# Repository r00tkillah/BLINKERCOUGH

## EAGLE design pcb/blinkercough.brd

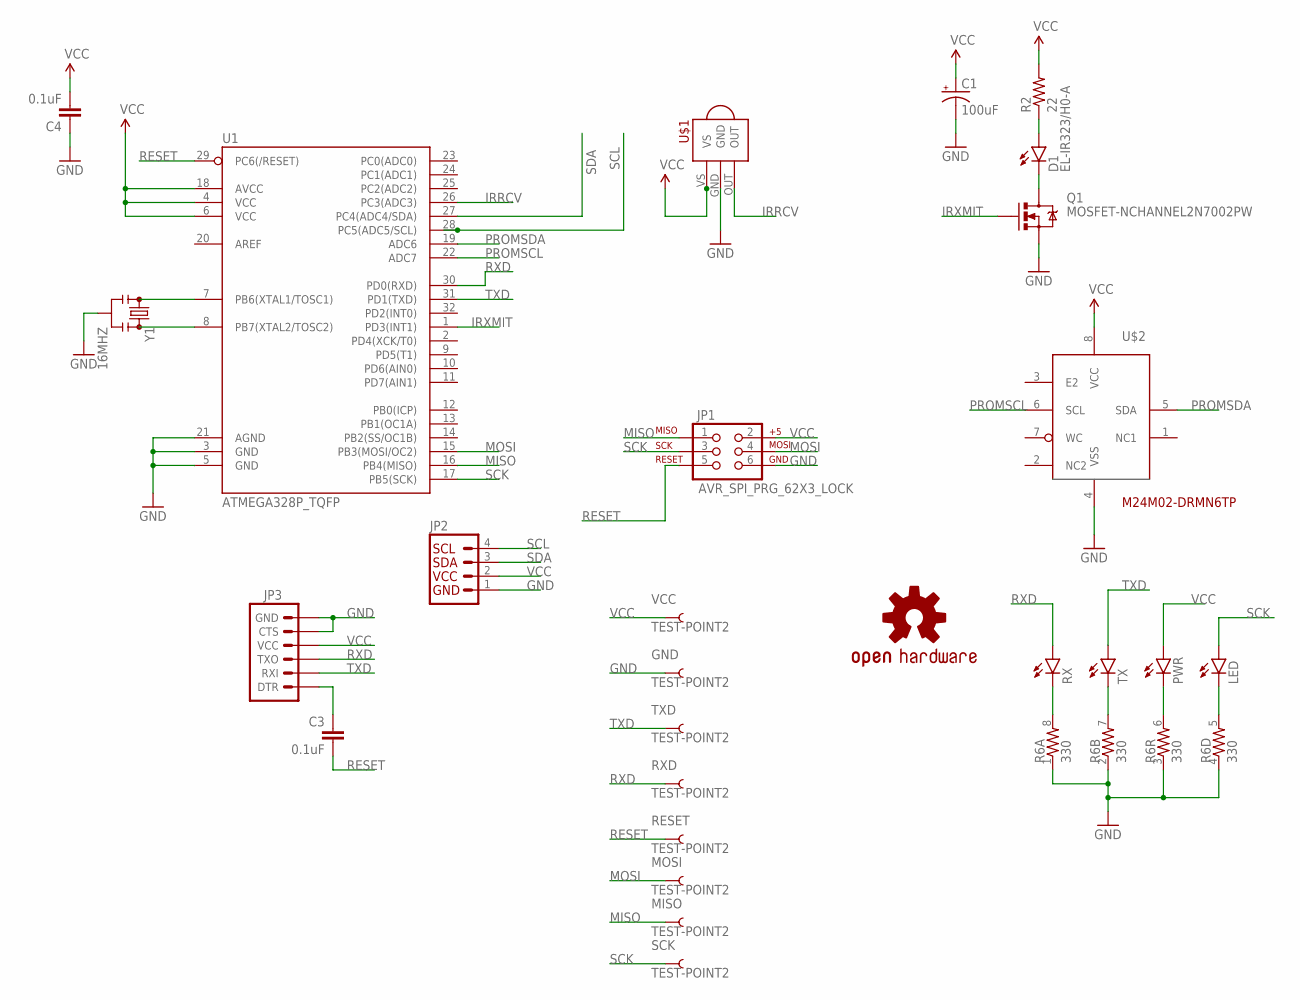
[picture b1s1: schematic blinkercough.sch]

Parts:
C1: 100uF; EIA7343
C3, C4: 0.1uF; 0603-CAP
D1: EL-IR323/H0-A; LED3MM
GND: TEST-POINT2; PAD.02X.02
JP1: AVR_SPI_PRG_62X3_LOCK; 2X3_LOCK
JP2: I2C_STANDARD; 1X04
JP3: ARDUINO_SERIAL_PROGRAMLOCK; 1X06_LOCK
LED: LED0603; LED-0603
LOGO1: OSHW-LOGOS; OSHW-LOGO-S
MISO: TEST-POINT2; PAD.02X.02
MOSI: TEST-POINT2; PAD.02X.02
PWR: LED0603; LED-0603
Q1: MOSFET-NCHANNEL2N7002PW; SOT323
R2: 22; 1206
R6: 330; 0603-ARV
RESET: TEST-POINT2; PAD.02X.02
RX: LED0603; LED-0603
RXD: TEST-POINT2; PAD.02X.02
SCK: TEST-POINT2; PAD.02X.02
TX: LED0603; LED-0603
TXD: TEST-POINT2; PAD.02X.02
U1: ATMEGA328P_TQFP; TQFP32-08
U$1: TSOP2438
U$2: M24M02-DRMN6TP; SO8
VCC: TEST-POINT2; PAD.02X.02
Y1: 16MHZ; RESONATOR-SMD

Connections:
GND: C1.C (-), C4.1, GND.P$1, JP1.6, JP2.1, JP3.5 (CTS), JP3.6 (GND), Q1.2 (S), R6.1, R6.2 (1), R6.3 (1), R6.4 (1), U1.3 (GND), U1.5 (GND), U1.21 (AGND), U$1.GND, U$2.4 (VSS), Y1.2
IRRCV: U1.26 (PC3(ADC3)), U$1.OUT
IRXMIT: Q1.1 (G), U1.1 (PD3(INT1))
LED: LED.C, R6.5 (2)
MISO: JP1.1, MISO.P$1, U1.16 (PB4(MISO))
MOSI: JP1.4, MOSI.P$1, U1.15 (PB3(MOSI/OC2))
unnamed: U1.7 (PB6(XTAL1/TOSC1)), Y1.1
unnamed: U1.8 (PB7(XTAL2/TOSC2)), Y1.3
unnamed: R6.8 (2), RX.C
unnamed: C3.1, JP3.1 (DTR)
unnamed: D1.K (C), Q1.3 (D)
unnamed: D1.A, R2.1
unnamed: R6.7 (2), TX.C
PROMSCL: U1.22 (ADC7), U$2.6 (SCL)
PROMSDA: U1.19 (ADC6), U$2.5 (SDA)
PWR: PWR.C, R6.6 (2)
RESET: C3.2, JP1.5, RESET.P$1, U1.29 (PC6(/RESET))
RXD: JP3.3 (TXO), RX.A, RXD.P$1, U1.30 (PD0(RXD))
SCK: JP1.3, LED.A, SCK.P$1, U1.17 (PB5(SCK))
SCL: JP2.4, U1.28 (PC5(ADC5/SCL))
SDA: JP2.3, U1.27 (PC4(ADC4/SDA))
TXD: JP3.2 (RXI), TX.A, TXD.P$1, U1.31 (PD1(TXD))
VCC: C1.A (+), C4.2, JP1.2, JP2.2, JP3.4 (VCC), PWR.A, R2.2, U1.4 (VCC), U1.6 (VCC), U1.18 (AVCC), U$1.VS, U$2.8 (VCC), VCC.P$1

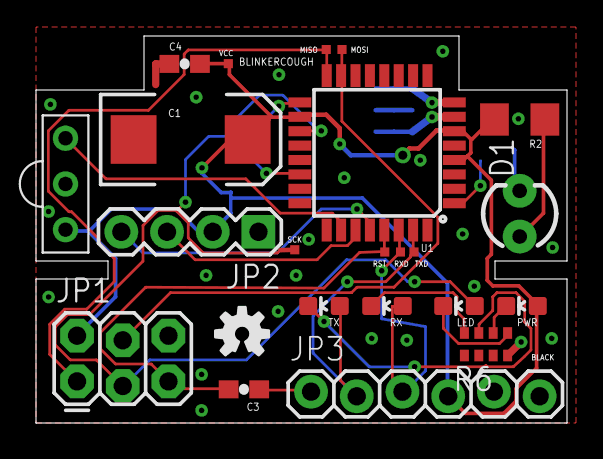
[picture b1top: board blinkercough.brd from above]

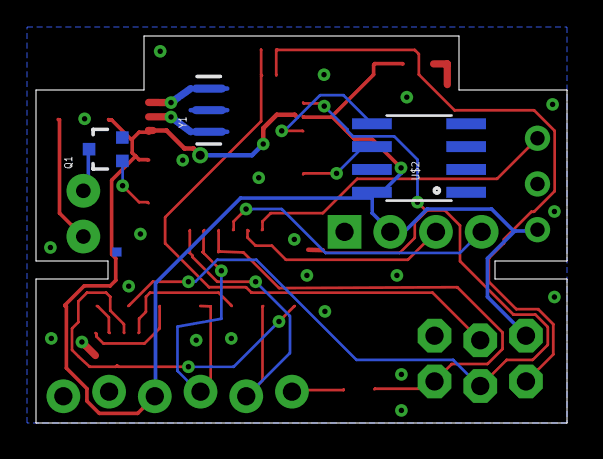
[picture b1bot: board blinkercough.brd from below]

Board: 2 copper layers, 29.5 x 21.5 mm, 27 parts (4 on the bottom side), 23 nets.

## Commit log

2015-08-10 Initial public push of BLINKERCOUGH
    BLINKERCOUGH is an NSA Playset project to bridge the airgap without
    radios. This was presented at BSidesLV 2015.
    There are still bugs with this release. This work is not finished.
2015-08-11 Adding eagle PCB design files
2015-08-21 fix submodules
    It appears that this was broken for new checkouts and I had failed to notice
2015-08-21 add address storage into eeprom to make life easier
2015-08-21 whitespace cleanup
2015-08-23 fix format string screwup in hexdump
2015-08-27 Fixes #3
    Actually it was not commander.py, but an off by one buffer length in
    the serial implementation of the registers in the main file.
2015-09-07 catch some cases where debug wasn't used right
2015-09-07 convert polling to repeat commands
    serial buffer is just 2 bytes. buffer was not serviced fast enough in
    some cases (cause not fully understood) and getting truncated. Now,
    if the command times out, we repeat.
2015-09-20 output when invalid command is recieved
2015-09-20 correct order of free in hooks
2015-09-20 Fix off by one errors
2015-09-20 switch to queing bytes via events
    takes queue operations out of the interrupt context in i2c
2015-09-20 add debug for buffer overrun
2015-09-20 zero out frame on alloc/free
2015-09-20 add reset() in some lost cases
2015-09-20 add debug where print was used
2015-09-20 less chatty
2015-09-20 make packet printing slightly easier to use
2015-09-20 correct sizing errors
    In various ways.. Ought to make this easier to read/use
2015-09-20 symbolic size calculation
    Easier to read?
2015-09-20 another math error
2015-09-20 add poll_for to poll for specific times
2015-09-20 more math fixes
2015-09-20 fixes/verbosity
2015-09-25 whitespace fix
2015-09-25 act on class, not object
2015-09-25 make send stuff send something where aligment is detectable
2015-09-25 adjust chattyness
2015-09-25 add poll_forever mechanism
2015-09-25 more chattyness adjustments
2015-09-25 FASTER!
2015-09-25 import needed module
2015-09-25 missing library
2015-09-25 print in handy hex format
2015-09-25 fix i2c reading
2015-09-26 dead beef fix
2015-09-26 spelling fix
2015-09-27 add new "secret" reset register
2015-09-27 don't relay your own packets
2015-09-28 328's are not really so fast

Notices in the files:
parts and their libraries:
SparkFun-Capacitors: Licensing: Creative Commons ShareAlike 4.0 International - https://creativecommons.org/licenses/by-sa/4.0
